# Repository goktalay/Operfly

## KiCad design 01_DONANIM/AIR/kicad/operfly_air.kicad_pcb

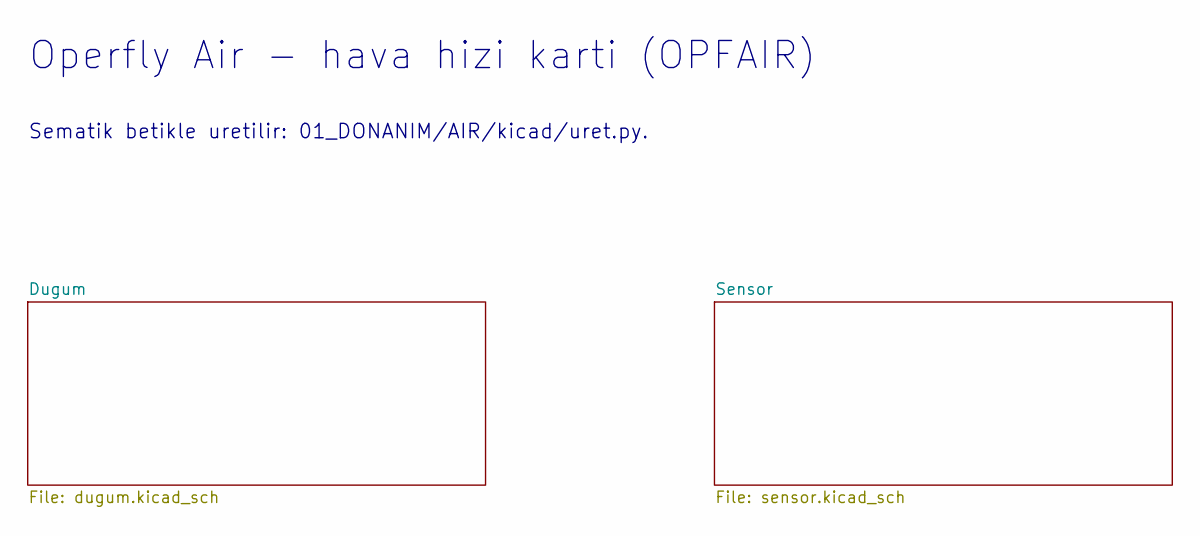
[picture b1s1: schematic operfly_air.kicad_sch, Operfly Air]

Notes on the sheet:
Operfly Air - hava hizi karti (OPFAIR)
Sematik betikle uretilir: 01_DONANIM/AIR/kicad/uret.py.

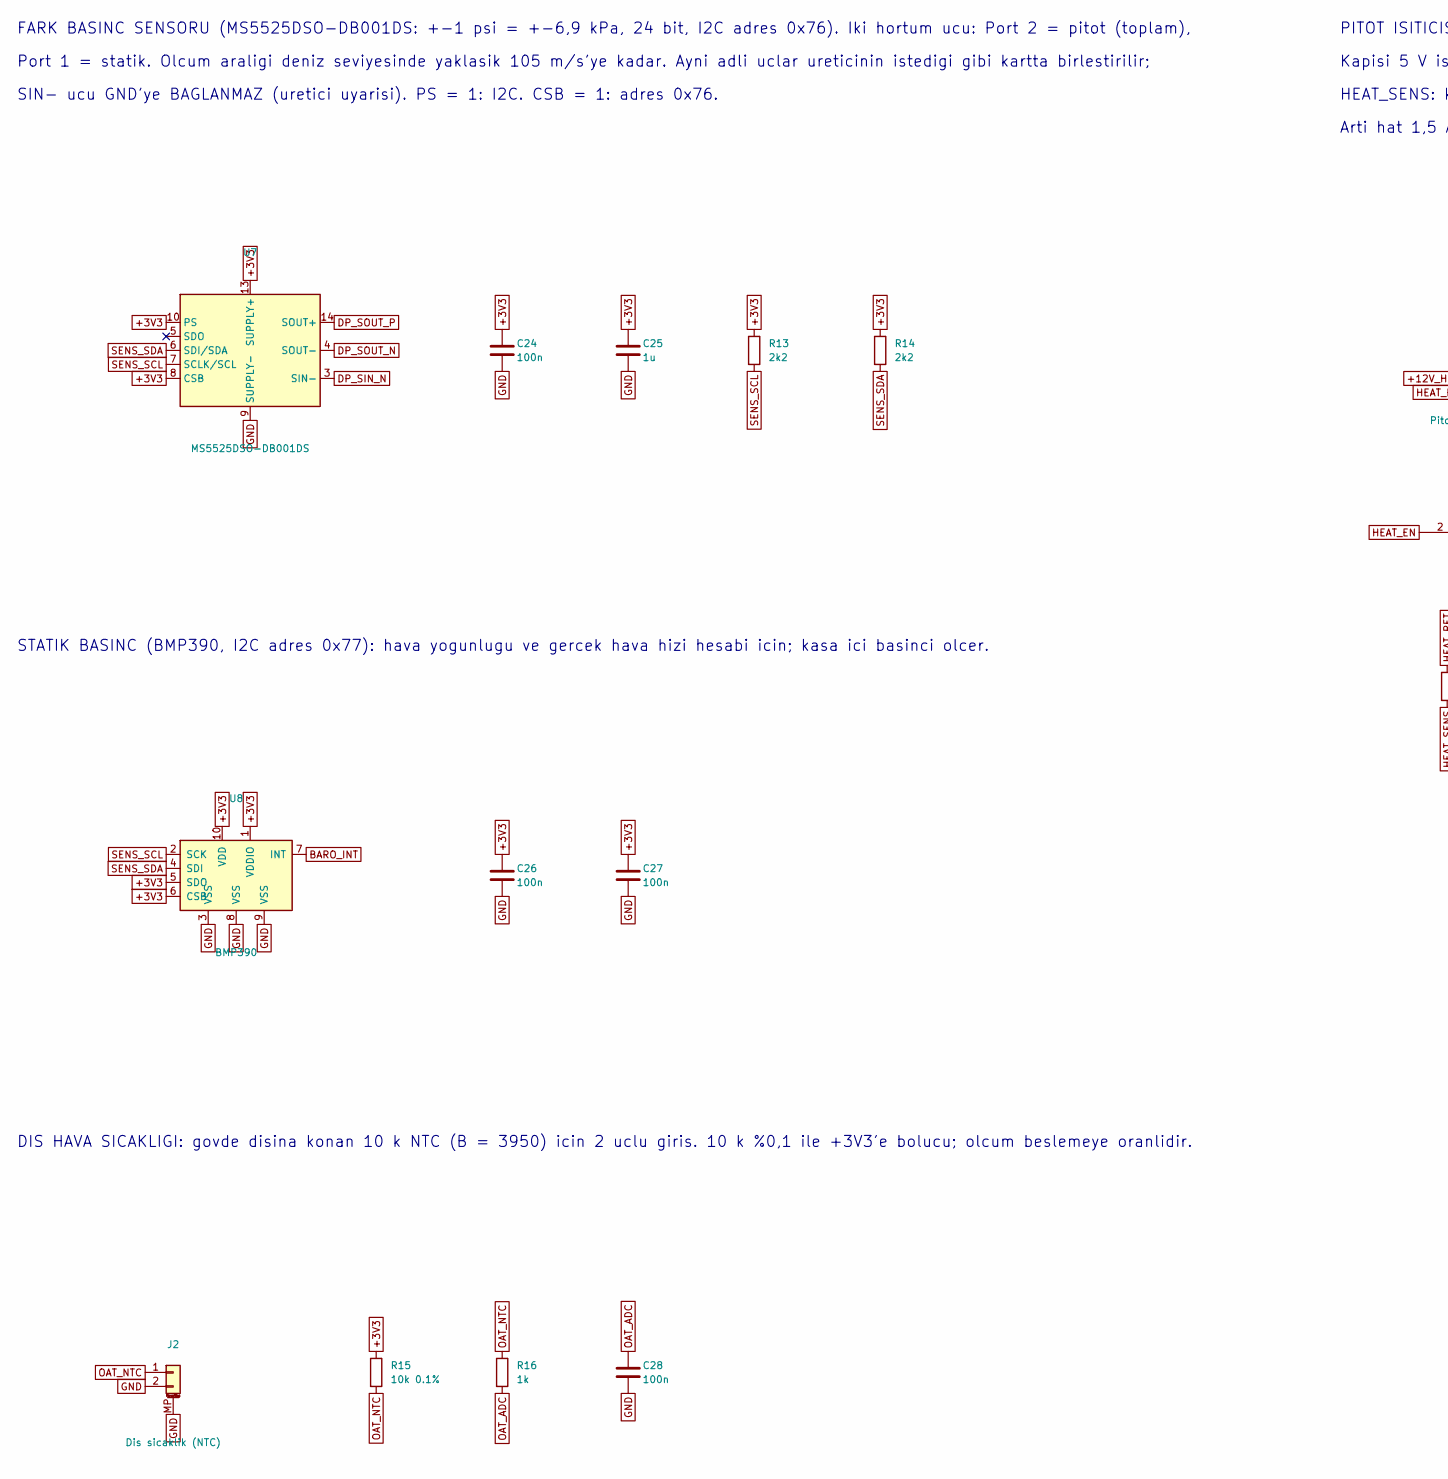
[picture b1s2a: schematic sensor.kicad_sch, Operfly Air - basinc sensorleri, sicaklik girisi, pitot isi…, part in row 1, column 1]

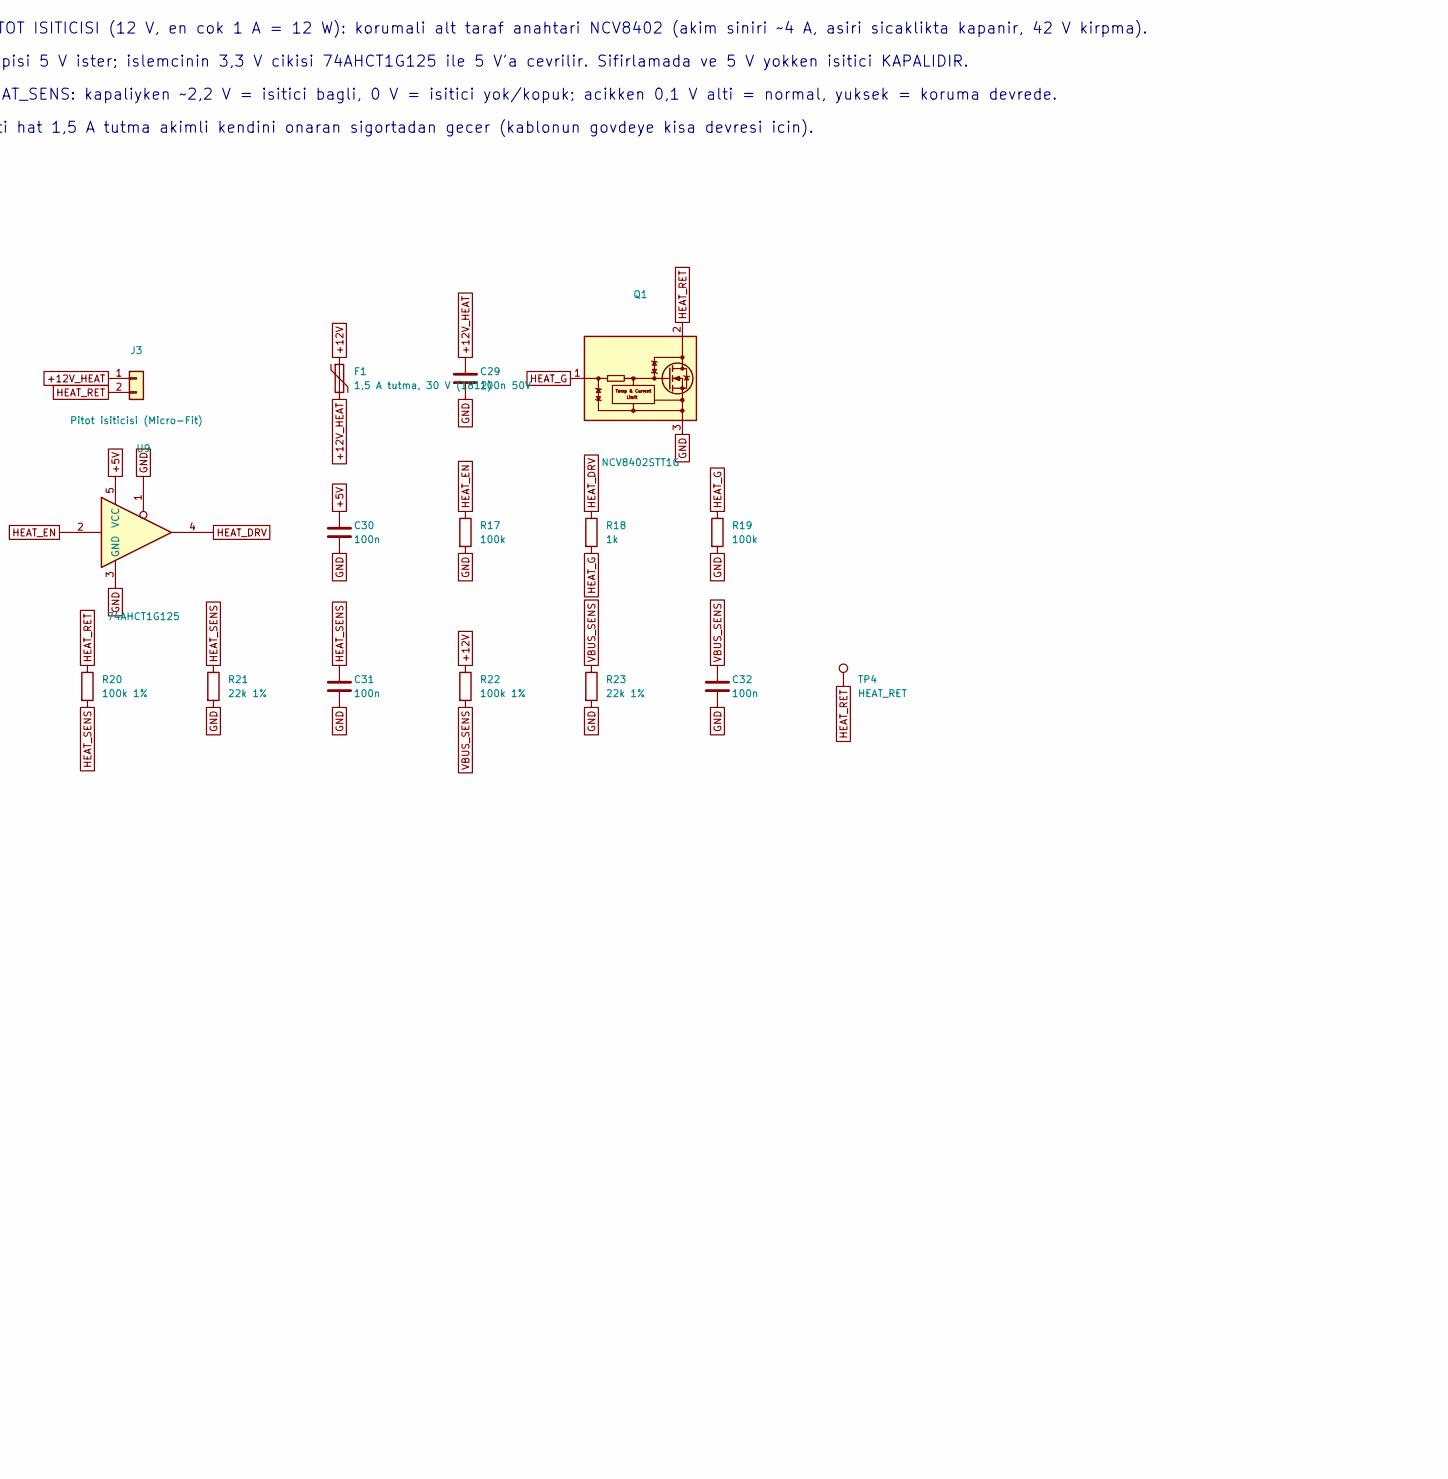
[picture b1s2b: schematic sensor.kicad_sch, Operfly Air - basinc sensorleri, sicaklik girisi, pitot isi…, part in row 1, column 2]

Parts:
C24, C26, C27, C28, C30, C31, C32: 100n; C_0402_1005Metric
C25: 1u; C_0402_1005Metric
C29: 100n 50V; C_0603_1608Metric
F1: 1,5 A tutma, 30 V (1812); Fuse_1812_4532Metric
J2: Dis sicaklik (NTC); JST_GH_SM02B-GHS-TB_1x02-1MP_P1.25mm_Horizontal
J3: Pitot isiticisi (Micro-Fit); Molex_Micro-Fit_3.0_43650-0200_1x02_P3.00mm_Horizontal
Q1: NCV8402STT1G; SOT-223
R13, R14: 2k2; R_0402_1005Metric
R15: 10k 0.1%; R_0402_1005Metric
R16, R18: 1k; R_0402_1005Metric
R17, R19: 100k; R_0402_1005Metric
R20, R22: 100k 1%; R_0402_1005Metric
R21, R23: 22k 1%; R_0402_1005Metric
TP4: HEAT_RET; TestPoint_Pad_D1.0mm
U7: MS5525DSO-DB001DS; TE_MS5525DSO-DBxxxyS
U8: BMP390; ST_HLGA-10_2x2mm_P0.5mm_LayoutBorder3x2y
U9: 74AHCT1G125; SOT-353_SC-70-5

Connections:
+3V3: C24.1, C25.1, C26.1, C27.1, R13.1, R14.1, R15.1, U7.8 (CSB), U7.10 (PS), U7.11 (SUPPLY+), U7.13 (SUPPLY+), U8.1 (VDDIO), U8.5 (SDO), U8.6 (CSB), U8.10 (VDD); also elsewhere on the board
+5V: C30.1, U9.5 (VCC); also elsewhere on the board
+12V: F1.1, R22.1; also elsewhere on the board
+12V_HEAT: C29.1, F1.2, J3.1
BARO_INT: U8.7 (INT); also elsewhere on the board
DP_SIN_N: U7.1 (SIN-), U7.3 (SIN-)
DP_SOUT_N: U7.2 (SOUT-), U7.4 (SOUT-)
DP_SOUT_P: U7.12 (SOUT+), U7.14 (SOUT+)
GND: C24.2, C25.2, C26.2, C27.2, C28.2, C29.2, C30.2, C31.2, C32.2, J2.2, J2.MP (MountPin), Q1.3 (S), R17.2, R19.2, R21.2, R23.2, U7.9 (SUPPLY-), U8.3 (VSS), U8.8 (VSS), U8.9 (VSS), U9.1, U9.3 (GND); also elsewhere on the board
HEAT_DRV: R18.1, U9.4
HEAT_EN: R17.1, U9.2; also elsewhere on the board
HEAT_G: Q1.1 (G), R18.2, R19.1
HEAT_RET: J3.2, Q1.2 (D), Q1.4 (D), R20.1, TP4.1
HEAT_SENS: C31.1, R20.2, R21.1; also elsewhere on the board
OAT_ADC: C28.1, R16.2; also elsewhere on the board
OAT_NTC: J2.1, R15.2, R16.1
SENS_SCL: R13.2, U7.7 (SCLK/SCL), U8.2 (SCK); also elsewhere on the board
SENS_SDA: R14.2, U7.6 (SDI/SDA), U8.4 (SDI); also elsewhere on the board
VBUS_SENS: C32.1, R22.2, R23.1; also elsewhere on the board

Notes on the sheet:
FARK BASINC SENSORU (MS5525DSO-DB001DS: +-1 psi = +-6,9 kPa, 24 bit, I2C adres 0x76). Iki hortum ucu: Port 2 = pitot (toplam),
PITOT ISITICISI (12 V, en cok 1 A = 12 W): korumali alt taraf anahtari NCV8402 (akim siniri ~4 A, asiri sicaklikta kapanir, 42 V kirpma).
Arti hat 1,5 A tutma akimli kendini onaran sigortadan gecer (kablonun govdeye kisa devresi icin).
SIN- ucu GND'ye BAGLANMAZ (uretici uyarisi). PS = 1: I2C. CSB = 1: adres 0x76.
Port 1 = statik. Olcum araligi deniz seviyesinde yaklasik 105 m/s'ye kadar. Ayni adli uclar ureticinin istedigi gibi kartta birlestirilir;
DIS HAVA SICAKLIGI: govde disina konan 10 k NTC (B = 3950) icin 2 uclu giris. 10 k %0,1 ile +3V3'e bolucu; olcum beslemeye oranlidir.
HEAT_SENS: kapaliyken ~2,2 V = isitici bagli, 0 V = isitici yok/kopuk; acikken 0,1 V alti = normal, yuksek = koruma devrede.
Kapisi 5 V ister; islemcinin 3,3 V cikisi 74AHCT1G125 ile 5 V'a cevrilir. Sifirlamada ve 5 V yokken isitici KAPALIDIR.
STATIK BASINC (BMP390, I2C adres 0x77): hava yogunlugu ve gercek hava hizi hesabi icin; kasa ici basinci olcer.

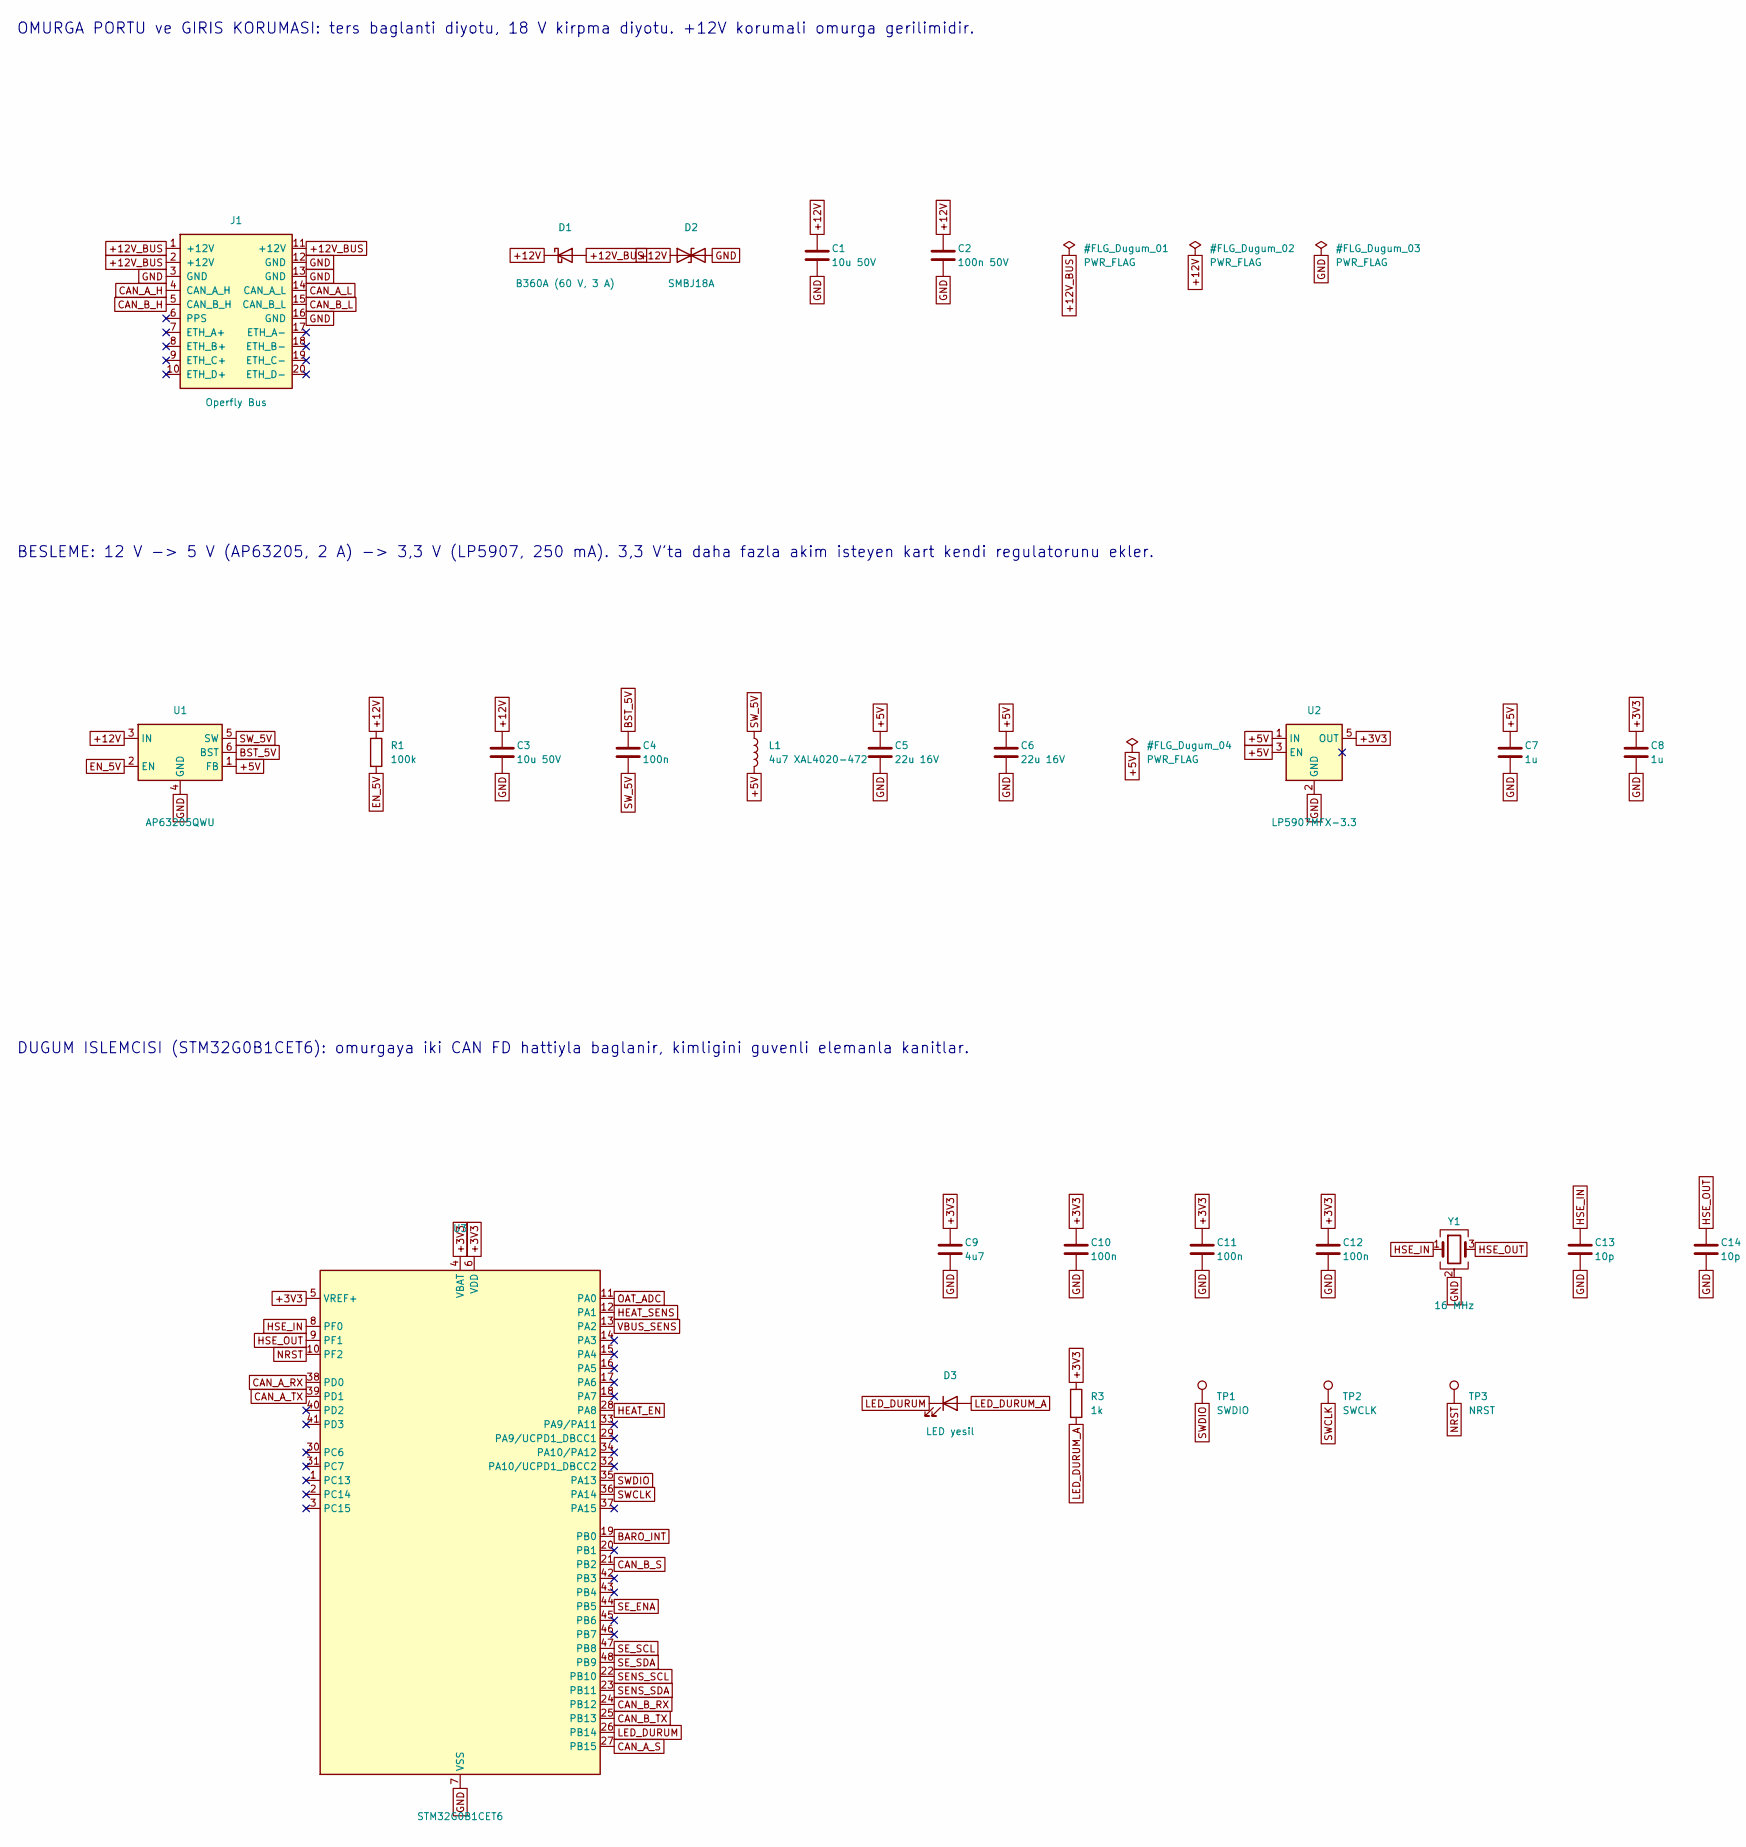
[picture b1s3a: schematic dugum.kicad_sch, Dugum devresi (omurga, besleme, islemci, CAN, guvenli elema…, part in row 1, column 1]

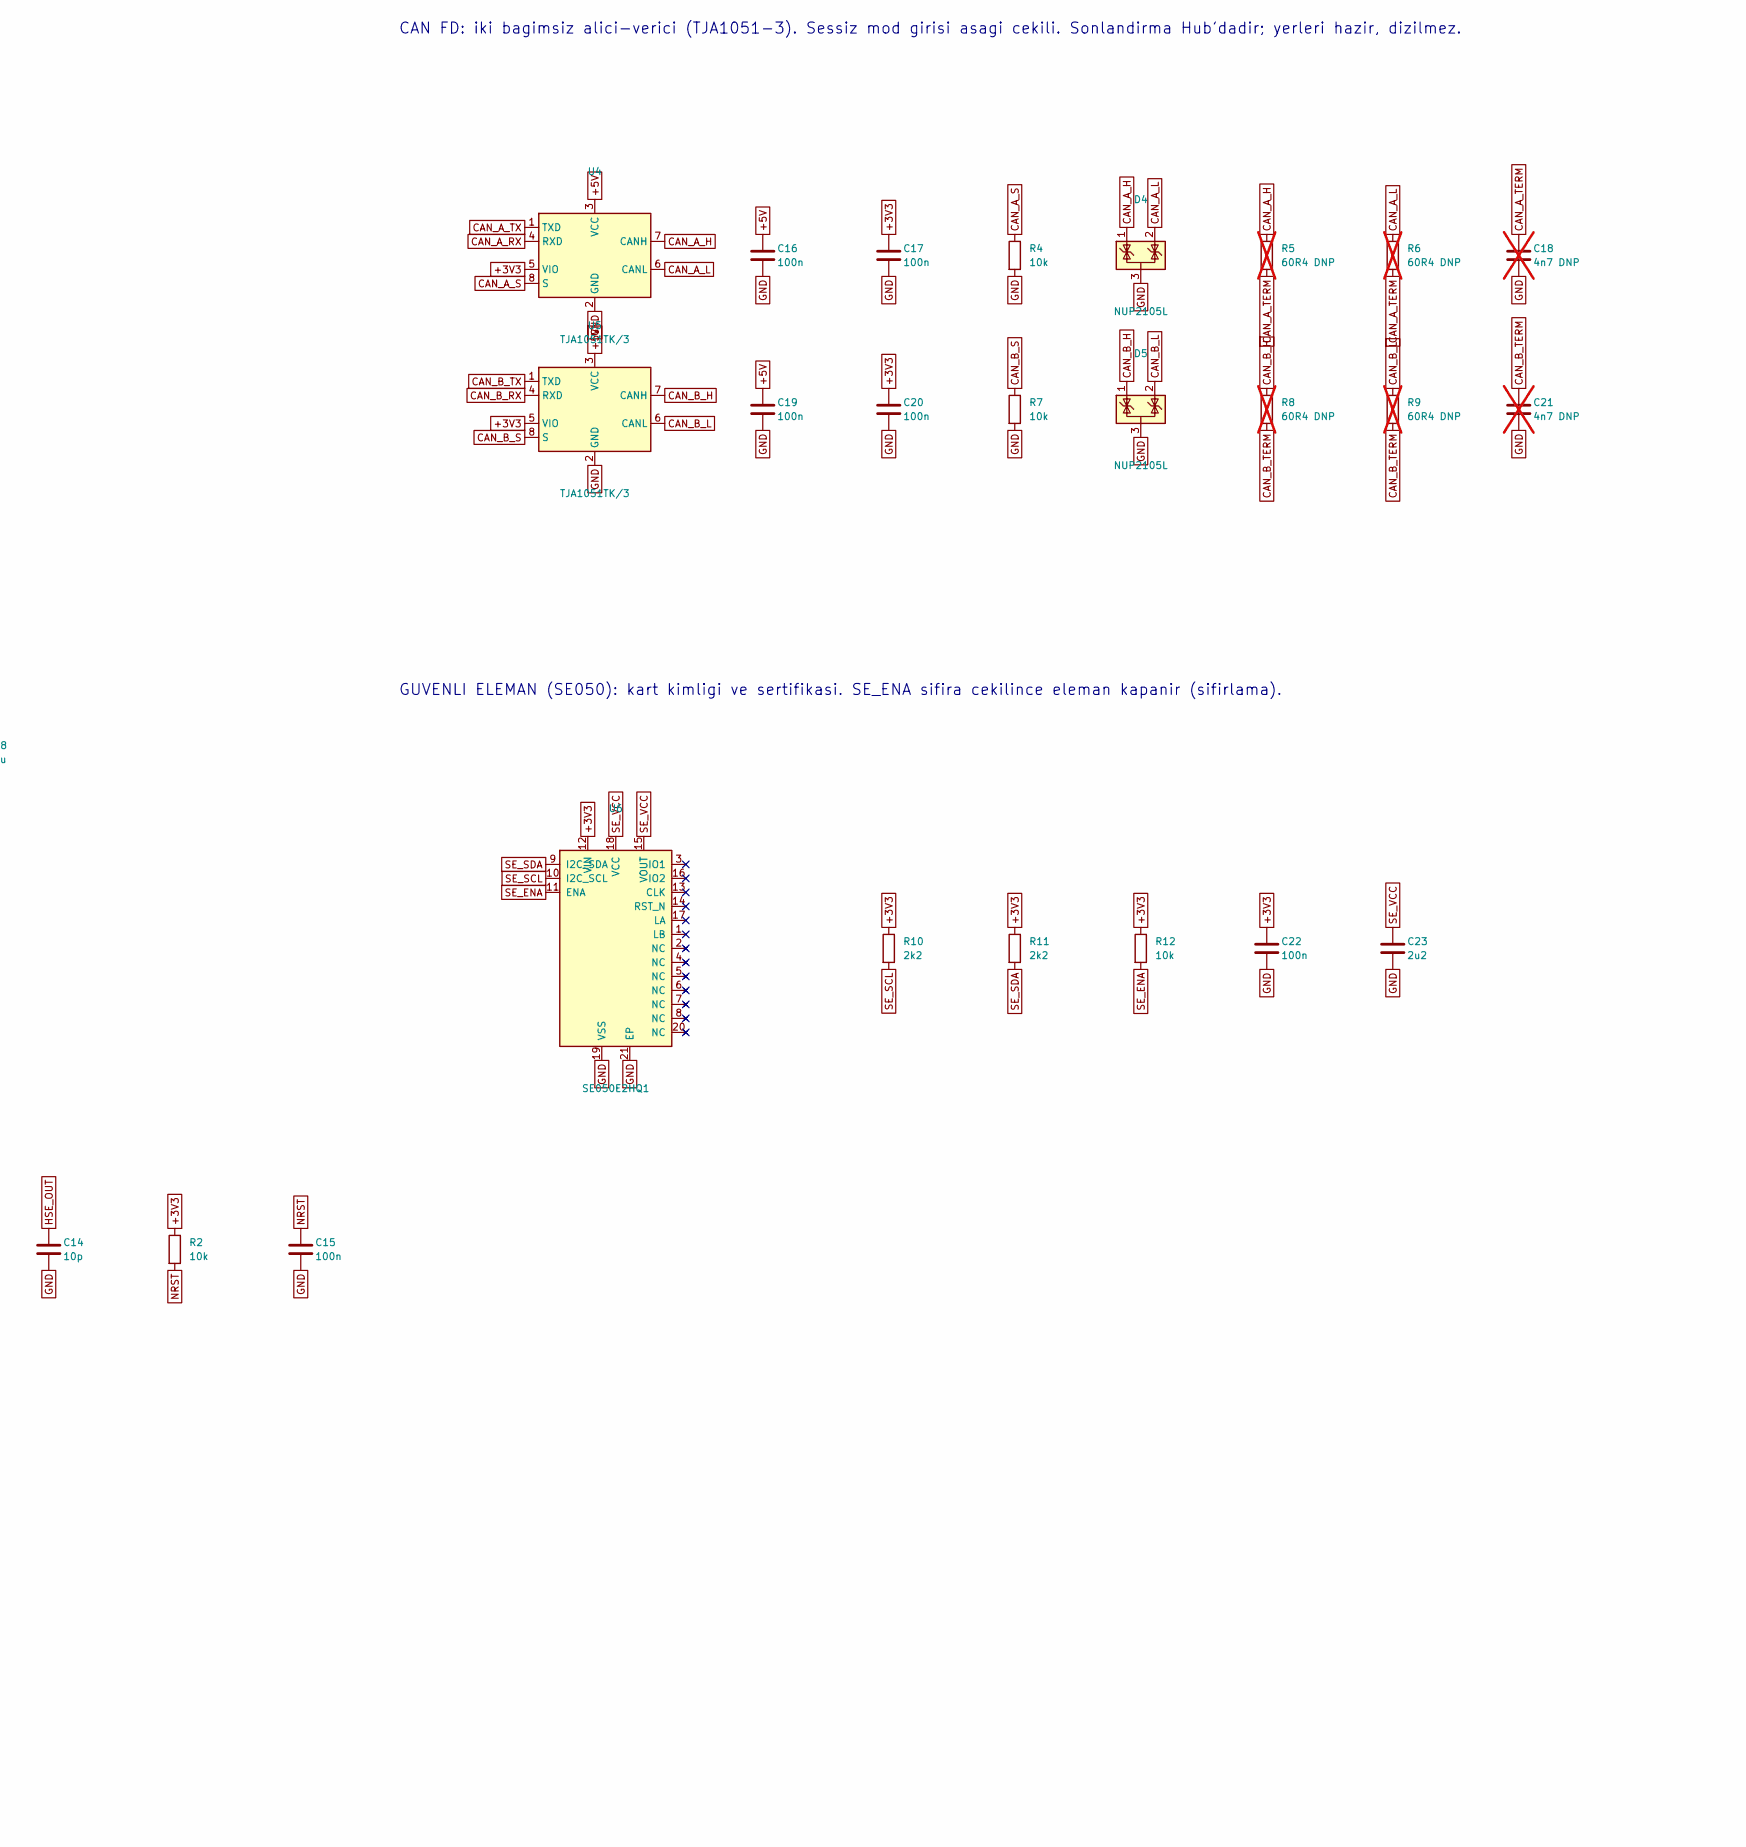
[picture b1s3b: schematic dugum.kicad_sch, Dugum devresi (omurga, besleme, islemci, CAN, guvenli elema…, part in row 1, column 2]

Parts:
C1, C3: 10u 50V; C_1206_3216Metric
C2: 100n 50V; C_0603_1608Metric
C4, C10, C11, C12, C15, C16, C17, C19, C20, C22: 100n; C_0402_1005Metric
C5, C6: 22u 16V; C_1206_3216Metric
C7, C8: 1u; C_0402_1005Metric
C9: 4u7; C_0603_1608Metric
C13, C14: 10p; C_0402_1005Metric
C18, C21: 4n7 DNP; C_0402_1005Metric; not fitted
C23: 2u2; C_0603_1608Metric
D1: B360A (60 V, 3 A); D_SMA
D2: SMBJ18A; D_SMB
D3: LED yesil; LED_0603_1608Metric
D4, D5: NUP2105L; SOT-23
J1: Operfly Bus; Harwin_Gecko_G125-MS12005M2P_2x10_P1.25mm_Vertical
L1: 4u7 XAL4020-472; L_Coilcraft_XAL4020-XXX
R1: 100k; R_0402_1005Metric
R2, R4, R7, R12: 10k; R_0402_1005Metric
R3: 1k; R_0402_1005Metric
R5, R6, R8, R9: 60R4 DNP; R_0402_1005Metric; not fitted
R10, R11: 2k2; R_0402_1005Metric
TP1: SWDIO; TestPoint_Pad_D1.0mm
TP2: SWCLK; TestPoint_Pad_D1.0mm
TP3: NRST; TestPoint_Pad_D1.0mm
U1: AP63205QWU; TSOT-23-6
U2: LP5907MFX-3.3; SOT-23-5
U3: STM32G0B1CET6; LQFP-48_7x7mm_P0.5mm
U4, U5: TJA1051TK/3; HVSON-8-1EP_3x3mm_P0.65mm_EP1.6x2.4mm
U6: SE050E2HQ1; QFN-20-1EP_3x3mm_P0.4mm_EP1.65x1.65mm
Y1: 16 MHz; Crystal_SMD_3225-4Pin_3.2x2.5mm

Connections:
+3V3: C8.1, C9.1, C10.1, C11.1, C12.1, C17.1, C20.1, C22.1, R2.1, R3.1, R10.1, R11.1, R12.1, U2.5 (OUT), U3.4 (VBAT), U3.5 (VREF+), U3.6 (VDD), U4.5 (VIO), U5.5 (VIO), U6.12 (VIN); also elsewhere on the board
+5V: C5.1, C6.1, C7.1, C16.1, C19.1, L1.2, U1.1 (FB), U2.1 (IN), U2.3 (EN), U4.3 (VCC), U5.3 (VCC); also elsewhere on the board
+12V: C1.1, C2.1, C3.1, D1.1 (K), D2.1 (A1), R1.1, U1.3 (IN); also elsewhere on the board
+12V_BUS: D1.2 (A), J1.1 (+12V), J1.2 (+12V), J1.11 (+12V)
BARO_INT: U3.19 (PB0); also elsewhere on the board
BST_5V: C4.1, U1.6 (BST)
CAN_A_H: D4.1 (K), J1.4 (CAN_A_H), R5.1, U4.7 (CANH)
CAN_A_L: D4.2 (K), J1.14 (CAN_A_L), R6.1, U4.6 (CANL)
CAN_A_RX: U3.38 (PD0), U4.4 (RXD)
CAN_A_S: R4.1, U3.27 (PB15), U4.8 (S)
CAN_A_TERM: C18.1, R5.2, R6.2
CAN_A_TX: U3.39 (PD1), U4.1 (TXD)
CAN_B_H: D5.1 (K), J1.5 (CAN_B_H), R8.1, U5.7 (CANH)
CAN_B_L: D5.2 (K), J1.15 (CAN_B_L), R9.1, U5.6 (CANL)
CAN_B_RX: U3.24 (PB12), U5.4 (RXD)
CAN_B_S: R7.1, U3.21 (PB2), U5.8 (S)
CAN_B_TERM: C21.1, R8.2, R9.2
CAN_B_TX: U3.25 (PB13), U5.1 (TXD)
EN_5V: R1.2, U1.2 (EN)
GND: C1.2, C2.2, C3.2, C5.2, C6.2, C7.2, C8.2, C9.2, C10.2, C11.2, C12.2, C13.2, C14.2, C15.2, C16.2, C17.2, C18.2, C19.2, C20.2, C21.2, C22.2, C23.2, D2.2 (A2), D4.3 (A), D5.3 (A), J1.3 (GND), J1.12 (GND), J1.13 (GND), J1.16 (GND), R4.2, R7.2, U1.4 (GND), U2.2 (GND), U3.7 (VSS), U4.2 (GND), U4.9 (GND), U5.2 (GND), U5.9 (GND), U6.19 (VSS), U6.21 (EP), Y1.2 (G), Y1.4 (G); also elsewhere on the board
HEAT_EN: U3.28 (PA8); also elsewhere on the board
HEAT_SENS: U3.12 (PA1); also elsewhere on the board
HSE_IN: C13.1, U3.8 (PF0), Y1.1
HSE_OUT: C14.1, U3.9 (PF1), Y1.3
LED_DURUM: D3.1 (K), U3.26 (PB14)
LED_DURUM_A: D3.2 (A), R3.2
NRST: C15.1, R2.2, TP3.1, U3.10 (PF2)
OAT_ADC: U3.11 (PA0); also elsewhere on the board
SENS_SCL: U3.22 (PB10); also elsewhere on the board
SENS_SDA: U3.23 (PB11); also elsewhere on the board
SE_ENA: R12.2, U3.44 (PB5), U6.11 (ENA)
SE_SCL: R10.2, U3.47 (PB8), U6.10 (I2C_SCL)
SE_SDA: R11.2, U3.48 (PB9), U6.9 (I2C_SDA)
SE_VCC: C23.1, U6.15 (VOUT), U6.18 (VCC)
SWCLK: TP2.1, U3.36 (PA14)
SWDIO: TP1.1, U3.35 (PA13)
SW_5V: C4.2, L1.1, U1.5 (SW)
VBUS_SENS: U3.13 (PA2); also elsewhere on the board

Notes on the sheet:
DUGUM ISLEMCISI (STM32G0B1CET6): omurgaya iki CAN FD hattiyla baglanir, kimligini guvenli elemanla kanitlar.
GUVENLI ELEMAN (SE050): kart kimligi ve sertifikasi. SE_ENA sifira cekilince eleman kapanir (sifirlama).
OMURGA PORTU ve GIRIS KORUMASI: ters baglanti diyotu, 18 V kirpma diyotu. +12V korumali omurga gerilimidir.
CAN FD: iki bagimsiz alici-verici (TJA1051-3). Sessiz mod girisi asagi cekili. Sonlandirma Hub'dadir; yerleri hazir, dizilmez.
BESLEME: 12 V -> 5 V (AP63205, 2 A) -> 3,3 V (LP5907, 250 mA). 3,3 V'ta daha fazla akim isteyen kart kendi regulatorunu ekler.

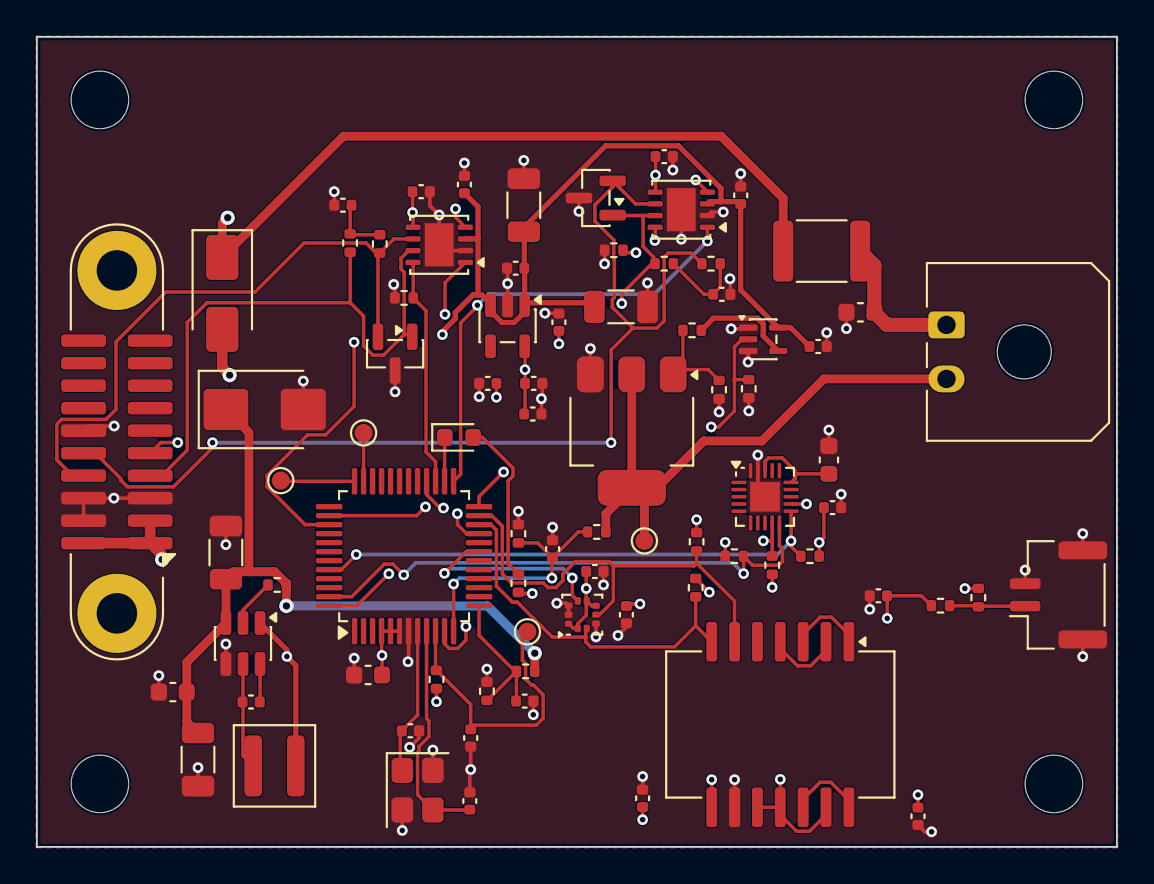
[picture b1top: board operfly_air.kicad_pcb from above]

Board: 4 copper layers, 60.0 x 45.0 mm, 84 parts (0 on the bottom side), 46 nets.

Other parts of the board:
H1, H2, H3, H4: M3; MountingHole_3.2mm_M3

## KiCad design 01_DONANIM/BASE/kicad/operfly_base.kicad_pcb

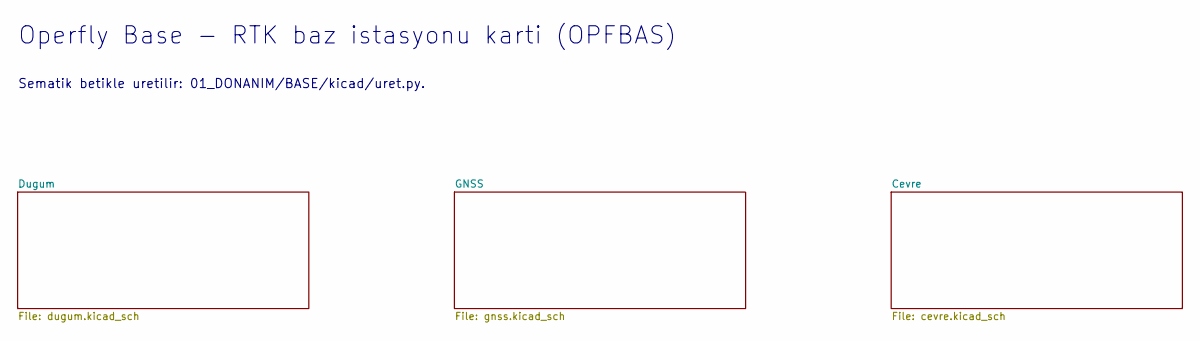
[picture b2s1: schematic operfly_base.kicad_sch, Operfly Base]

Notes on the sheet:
Sematik betikle uretilir: 01_DONANIM/BASE/kicad/uret.py.
Operfly Base - RTK baz istasyonu karti (OPFBAS)
